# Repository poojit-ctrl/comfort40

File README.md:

# Comfort40

Comfort40 is a compact 40-key mechanical keyboard designed to ditch all the bloat and keep only what matters. It’s got the vibe of minimalism with just enough muscle to handle your everyday typing, coding, shortcut-spamming, and layer-fu. Built for chill, built for speed, built for the desk setups that scream “I know what I’m doing.”

---

## What Even Is This

Comfort40 is a DIY keyboard project for anyone who’s ever looked at a full-size keyboard and thought “nah.” It’s a 40% board, ortholinear (so all the keys line up like a grid), and completely open source. You can build it however you like solder or hotswap, loud clicky switches or silent stealthy ones. It’s your call.

This board runs QMK and VIA, so you can customize literally every key. Layer keys? Macro madness? Tap dance? Yeah, it’s all here. Want a numpad? Put it on a layer. Arrows? You bet. The layout may be tiny but the power is unhinged.

---

## The Vibe

Comfort40 is designed in KiCad, modeled in Fusion 360, and 100% meant to be hacked on. The case is 3D printable, the plate is laser cuttable.
---

## Build Stats

layout → 4x10 grid  
switches → MX-style 
controller → RP2040  
port → USB-C  
pcb → hotswap  
NO RGB THO  
case → printable 
firmware → QMK + VIA

---
| Component                  | Description                                      | Qty | Estimated Price (USD) | Notes |
|---------------------------|--------------------------------------------------|-----|------------------------|-------|
| **PCB**                   | Custom Comfort40 PCB                             | 1   | $30.00(after coupon)   | From JLCPCB or similar |
| **Microcontroller**       | RP2040                                           | 1   | $2.00                  | USB-C |
| **Switches**              | MX-compatible mechanical switches                | 40  | $20.00                 | Gateron|
| **Keycaps**               | 40-key ortholinear set                           | 1   | $23.00                 | XDA/DSA works well |
| **Diodes**                | 1N4148                                           | 40  | $3.00                  | Through-hole or SMD |
| **Reset Switch**          | Tactile momentary switch                         | 1   | $0.50                  | Used for flashing |
| **Hotswap Sockets**       | Kailh MX hotswap sockets                         | 40  | $8.00                  | Why not |
| **Plate**                 | Laser-cut acrylic or FR4                         | 1   | $6.00                  | DXF included |
| **Case (Top + Bottom)**   | 3D printed or resin enclosure                    | 1   | $18.00                 | Print or outsource |
| **Screws/Standoffs**      | M3 hardware                                      | 1 set | $2.00                | For mounting everything |
| **USB Cable**             | USB-C to USB-A cable                             | 1   | $4.00                  | Any decent one |
| **Rotary Encoder**        | EC11 vertical rotary encoder                     | 1   | $2.00                  | Includes push button switch |
| **Knob Cap**              | Aluminum or plastic vertical knob                | 1   | $1.50                  | Press-fit or set screw type |
| **Foam/Dampening**        | EVA foam or PE sheet                             | 1   | ALREADY HAVE IT AT HOME| silencing mod |

---
## Estimated Total: **$120.00 USD**

## Images

## Fully Assembled Render  
| Image | Description |
|-------|-------------|
|  | A render straight outta Fusion 360. You’re looking at the full Comfort40 in all its glory, keycaps and all. |

## PCB  
| Image | Description |
|-------|-------------|
|  | KiCad PCB layout. Shows the switch footprint grid, MCU spot, USB traces, and that crispy clean diode matrix. |

## Schematic  
| Image | Description |
|-------|-------------|
|  | The full wiring brain. Every connection from switch to controller. Diodes, resistors, reset, and the rest. |

## KiCad 3D View  
| Image | Description |
|-------|-------------|
|  | The raw KiCad 3D preview. Check that switch layout and component placement. No case here, just vibes. |

## Hot swappable
| Image | Description |
|-------|-------------|
|  | KLE Layout |

---

## Flashing the Brain

QMK is the default brain of Comfort40. Flash it with QMK Toolbox or VIA Configurator

---

## Who It’s For

- people who like small keyboards  
- people who like building stuff  
- people who hate reaching for arrow keys  
- people who want full power in a tiny square of plastic  
- also people who just want a reason to use their soldering iron again

---

## Licence

MIT

made for comfort not clutter  
zero bloat  
just keys

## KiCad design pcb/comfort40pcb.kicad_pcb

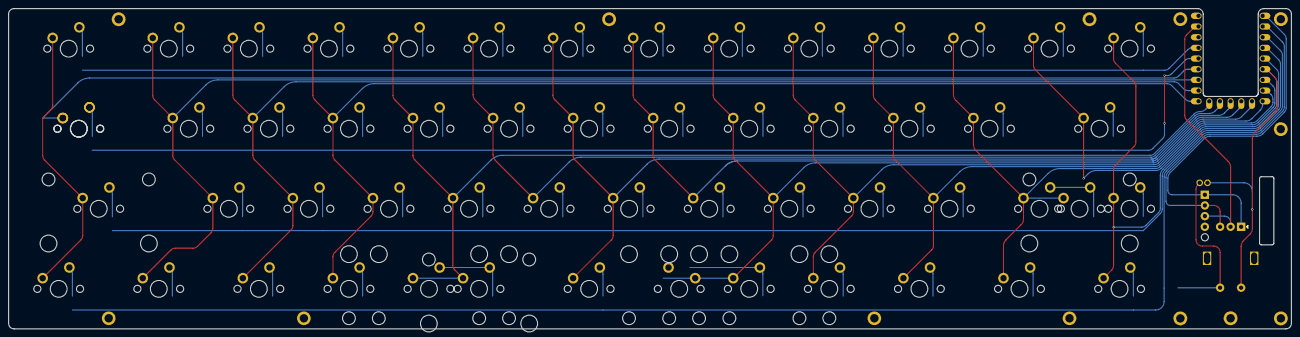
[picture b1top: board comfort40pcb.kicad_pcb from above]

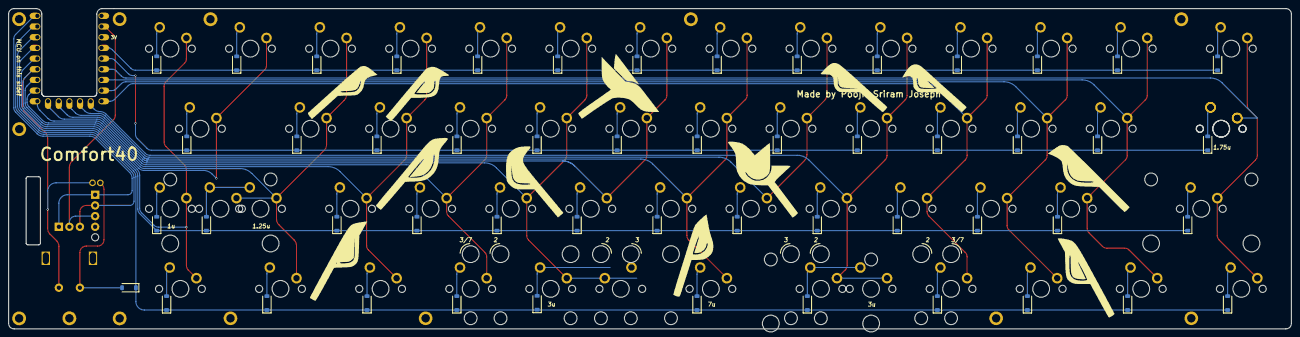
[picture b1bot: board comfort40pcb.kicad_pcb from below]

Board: 2 copper layers, 305.2 x 76.2 mm, 113 parts (52 on the bottom side), 73 nets.

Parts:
D1, D2, D3, D4, D5, D6, D7, D8, D9, D10, D11, D12, D13, D14, D15, D16, D17, D18, D19, D20, D21, D22, D23, D24, D25, D26, D27, D28, D29, D30, D31, D32, D33, D34, D35, D36, D37, D38, D39, D40, D41, D42, D43, D44, D45, D46, D47, D48, D49, D50, D51, D52: 1N4148W; D_SOD-123
MP: (no value)
SW1: MX150
SW2, SW3#2, SW4, SW5, SW6, SW7, SW8, SW9, SW10, SW11, SW12, SW13, SW14, SW16, SW17, SW18, SW19, SW20, SW21, SW22, SW23, SW24, SW25, SW26, SW29, SW30, SW31, SW32, SW33, SW34, SW35, SW36, SW37, SW38, SW45, SW50: MX100
SW3: Rotary_Encoder_Switch; EVQWGD001
SW15: Stepped; MX175
SW27: MX175
SW28: MX225R; MX225
SW39: 1.25u; MX125
SW40, SW47: 2.25u; MX225
SW41: 1u; MX100
SW42, SW43, SW44, SW51, SW52, SW53: MX125
SW46, SW49: 3u; MX300R
SW48: 7u; MX100
SW54: 2.75u; MX275R
SW55: RotaryEncoder_Switch; RotaryEncoder_Alps_EC11E-Switch_Vertical_H20mm
SW55#2: 1.75u; MX175
SW**: MX200R
SW**#2: MX200R
U1: RP2040-Zero; MCU_rp2040-zero-tht

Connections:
COL0: SW1.2 (Row), SW15.2 (Row), SW28.2 (Row), SW42.2 (Row), SW55#2.2
COL1: SW2.2 (Row), SW16.2 (Row), SW29.2 (Row), SW43.2 (Row)
COL2: SW3#2.2 (Row), SW17.2 (Row), SW30.2 (Row), SW44.2 (Row), U1.15
COL3: SW4.2 (Row), SW18.2 (Row), SW31.2 (Row), SW45.2 (Row), U1.14
COL4: SW5.2 (Row), SW19.2 (Row), SW32.2 (Row), SW46.2 (Row), SW47.2 (Row), U1.13
COL5: SW6.2 (Row), SW20.2 (Row), SW33.2 (Row), U1.12
COL6: SW7.2 (Row), SW21.2 (Row), SW34.2 (Row), SW48.2 (Row), U1.11
COL7: SW8.2 (Row), SW22.2 (Row), SW35.2 (Row), U1.10
COL8: SW9.2 (Row), SW23.2 (Row), SW36.2 (Row), SW49.2 (Row), SW54.2 (Row), U1.9
COL9: SW10.2 (Row), SW24.2 (Row), SW37.2 (Row), SW50.2 (Row), U1.8
COL10: SW11.2 (Row), SW25.2 (Row), SW38.2 (Row), SW51.2 (Row), U1.7
COL11: SW12.2 (Row), SW26.2 (Row), SW39.2 (Row), SW40.2 (Row), SW52.2 (Row), U1.6
COL12: SW3.S2, SW13.2 (Row), SW27.2 (Row), SW55.S2, U1.5
COL13: SW14.2 (Row), SW41.2 (Row), SW53.2 (Row), U1.4
ENC_CCW: SW3.A, SW55.A
ENC_CW: SW3.B, SW55.B, U1.1
GND: SW3.C, SW55.C
unnamed: D1.2 (A), SW1.1 (Col)
unnamed: D2.2 (A), SW2.1 (Col)
unnamed: D3.2 (A), SW3#2.1 (Col)
unnamed: D4.2 (A), SW4.1 (Col)
unnamed: D5.2 (A), SW5.1 (Col)
unnamed: D6.2 (A), SW6.1 (Col)
unnamed: D7.2 (A), SW7.1 (Col)
unnamed: D8.2 (A), SW8.1 (Col)
unnamed: D9.2 (A), SW9.1 (Col)
unnamed: D10.2 (A), SW10.1 (Col)
unnamed: D11.2 (A), SW11.1 (Col)
unnamed: D12.2 (A), SW12.1 (Col)
unnamed: D13.2 (A), SW13.1 (Col)
unnamed: D14.2 (A), SW14.1 (Col)
unnamed: D15.2 (A), SW15.1 (Col), SW55#2.1
unnamed: D16.2 (A), SW16.1 (Col)
unnamed: D17.2 (A), SW17.1 (Col)
unnamed: D18.2 (A), SW18.1 (Col)
unnamed: D19.2 (A), SW19.1 (Col)
unnamed: D20.2 (A), SW20.1 (Col)
unnamed: D21.2 (A), SW21.1 (Col)
unnamed: D22.2 (A), SW22.1 (Col)
unnamed: D23.2 (A), SW23.1 (Col)
unnamed: D24.2 (A), SW24.1 (Col)
unnamed: D25.2 (A), SW25.1 (Col)
unnamed: D26.2 (A), SW26.1 (Col)
unnamed: D27.2 (A), SW27.1 (Col)
unnamed: D28.2 (A), SW28.1 (Col)
unnamed: D29.2 (A), SW29.1 (Col)
unnamed: D30.2 (A), SW30.1 (Col)
unnamed: D31.2 (A), SW31.1 (Col)
unnamed: D32.2 (A), SW32.1 (Col)
unnamed: D33.2 (A), SW33.1 (Col)
unnamed: D34.2 (A), SW34.1 (Col)
unnamed: D35.2 (A), SW35.1 (Col)
unnamed: D36.2 (A), SW36.1 (Col)
unnamed: D37.2 (A), SW37.1 (Col)
unnamed: D38.2 (A), SW38.1 (Col)
unnamed: D39.2 (A), SW39.1 (Col), SW40.1 (Col)
unnamed: D40.2 (A), SW3.S1, SW55.S1
unnamed: D41.2 (A), SW41.1 (Col)
unnamed: D42.2 (A), SW53.1 (Col)
unnamed: D43.2 (A), SW52.1 (Col)
unnamed: D44.2 (A), SW51.1 (Col)
unnamed: D45.2 (A), SW50.1 (Col)
unnamed: D46.2 (A), SW49.1 (Col), SW54.1 (Col)
unnamed: D47.2 (A), SW48.1 (Col)
unnamed: D48.2 (A), SW46.1 (Col), SW47.1 (Col)
unnamed: D49.2 (A), SW45.1 (Col)
unnamed: D50.2 (A), SW44.1 (Col)
unnamed: D51.2 (A), SW43.1 (Col)
unnamed: D52.2 (A), SW42.1 (Col)
ROW0: D1.1 (K), D2.1 (K), D3.1 (K), D4.1 (K), D5.1 (K), D6.1 (K), D7.1 (K), D8.1 (K), D9.1 (K), D10.1 (K), D11.1 (K), D12.1 (K), D13.1 (K), D14.1 (K)
ROW1: D15.1 (K), D16.1 (K), D17.1 (K), D18.1 (K), D19.1 (K), D20.1 (K), D21.1 (K), D22.1 (K), D23.1 (K), D24.1 (K), D25.1 (K), D26.1 (K), D27.1 (K)
ROW2: D28.1 (K), D29.1 (K), D30.1 (K), D31.1 (K), D32.1 (K), D33.1 (K), D34.1 (K), D35.1 (K), D36.1 (K), D37.1 (K), D38.1 (K), D39.1 (K), D41.1 (K), U1.3
ROW3: D40.1 (K), D42.1 (K), D43.1 (K), D44.1 (K), D45.1 (K), D46.1 (K), D47.1 (K), D48.1 (K), D49.1 (K), D50.1 (K), D51.1 (K), D52.1 (K), U1.2
